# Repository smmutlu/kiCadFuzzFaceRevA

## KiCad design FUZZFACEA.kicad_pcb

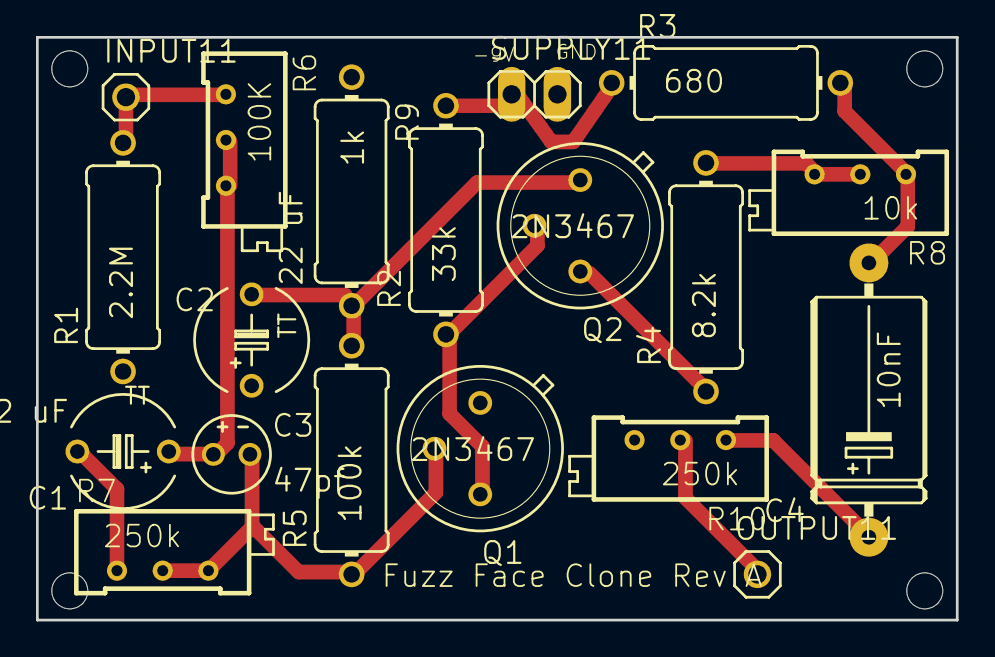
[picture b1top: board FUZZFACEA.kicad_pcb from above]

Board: 2 copper layers, 51.1 x 32.4 mm, 23 parts (0 on the bottom side), 13 nets.

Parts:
@HOLE0, @HOLE1, @HOLE2, @HOLE3: (no value)
C1: 2.2 uF; TAP5-60
C2: 22 uF; TAP5-60
C3: 47pf; E2-4
C4: 10nF; E15-6
INPUT11: 1X01
OUTPUT11: 1X01
Q1, Q2: 2N3467; TO39
R1: 2.2M; 0411%2f12
R2: 33k; 0411%2f12
R3: 680; 0411%2f12
R4: 8.2k; 0411%2f12
R5: 100k; 0411%2f12
R6: 100K; RTRIM64X
R7, R10: 250k; RTRIM64X
R8: 10k; RTRIM64X
R9: 1k; 0411%2f12
SUPPLY11: 1X02

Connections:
-9V: R2.2, R3.1, SUPPLY11.1
GND: C2.+, Q1.1, R1.1, R9.1, R10.3, SUPPLY11.2
INPUT: INPUT11.1, R1.2, R6.1
N1: C1.+, C3.+, R6.2, R6.3
N2: C1.-, R7.1
N3: C3.-, Q1.2, R5.1, R7.2, R7.3
N4: C2.-, Q2.1, R5.2, R9.2
N5: Q1.3, Q2.2, R2.1
N6: Q2.3, R4.1
N7: R4.2, R8.2, R8.3
N8: C4.-, R3.2, R8.1
N9: C4.+, R10.1
OUTPUT: OUTPUT11.1, R10.2

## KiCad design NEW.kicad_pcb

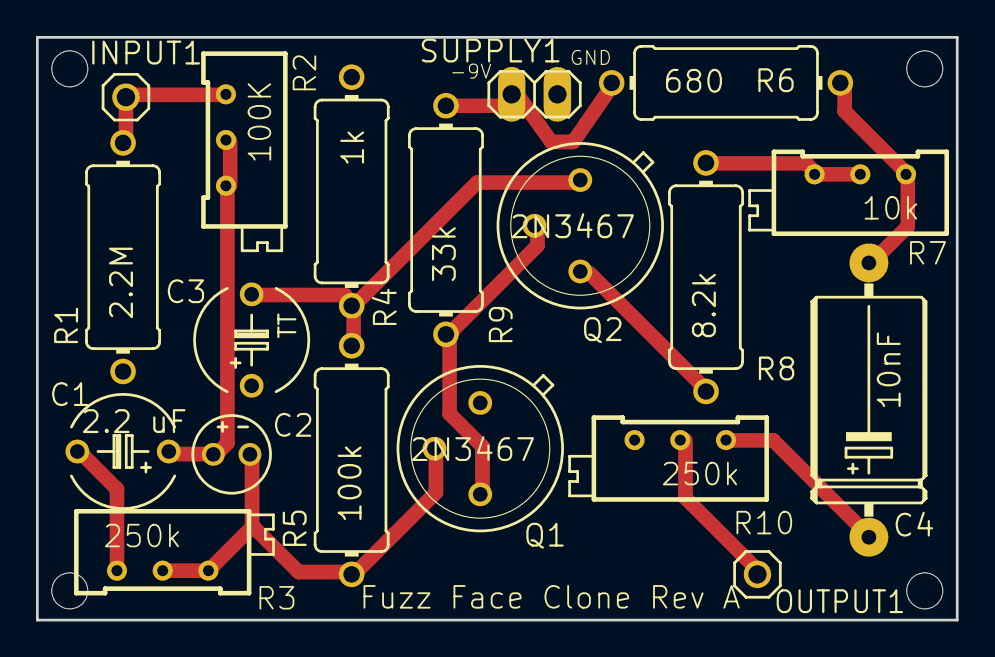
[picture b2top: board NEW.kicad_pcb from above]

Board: 2 copper layers, 51.1 x 32.4 mm, 23 parts (0 on the bottom side), 13 nets.

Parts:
@HOLE0, @HOLE1, @HOLE2, @HOLE3: (no value)
C1: 2.2 uF; TAP5-60
C2: E2-4
C3: TAP5-60
C4: 10nF; E15-6
INPUT1: 1X01
OUTPUT1: 1X01
Q1, Q2: 2N3467; TO39
R1: 2.2M; 0411%2f12
R2: 100K; RTRIM64X
R3, R10: 250k; RTRIM64X
R4: 33k; 0411%2f12
R5: 100k; 0411%2f12
R6: 680; 0411%2f12
R7: 10k; RTRIM64X
R8: 8.2k; 0411%2f12
R9: 1k; 0411%2f12
SUPPLY1: 1X02

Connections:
-9V: R4.2, R6.1, SUPPLY1.1
/INPUT: INPUT1.1, R1.2, R2.1
/N1: C1.+, C2.+, R2.2, R2.3
/N2: C1.-, R3.1
/N3: C2.-, Q1.2, R3.2, R3.3, R5.1
/N4: C3.-, Q2.1, R5.2, R9.2
/N5: Q1.3, Q2.2, R4.1
/N6: Q2.3, R8.1
/N7: R7.2, R7.3, R8.2
/N8: C4.-, R6.2, R7.1
/N9: C4.+, R10.1
/OUTPUT: OUTPUT1.1, R10.2
GND: C3.+, Q1.1, R1.1, R9.1, R10.3, SUPPLY1.2

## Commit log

2018-04-14 Init
